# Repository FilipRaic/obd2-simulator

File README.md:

# OBD-II Simulator

Open-source OBD-II simulator board that answers a diagnostic tool over CAN
exactly as a vehicle ECU does. The repository has three parts:

- the **protocol core** (`include/`, `src/`, `tests/`) - portable,
  host-testable protocol and simulation layers with no external
  dependencies, described below,
- the **firmware** (`firmware/`) - PlatformIO project for the device
  itself (FreeRTOS tasks, MCP2515 SPI driver, TFT_eSPI user interface,
  16 MB SPI NOR flash storage with USB-C MSC / USB-A stick transfer), which
  compiles the core unchanged and plugs into it through the small set of
  `extern` platform hooks listed below. See `firmware/README.md`,
- the **board** (`hardware/`) - the KiCad project, gerbers, bill of
  materials and the scripts that generate the board, at revision **v0.7**
  (130 x 115 mm, two-layer FR4, ESP32-S3-WROOM-1). See `hardware/README.md`.

The simulator answers a diagnostic tool over CAN and, like a real vehicle, powers
it from pin 16 of the J1962 connector. The protocol core described below is what
runs inside the "Microcontroller" block, and everything around it is documented
in [`hardware/README.md`](hardware/README.md), which walks through the same
schematics one design decision at a time.

Everything in the repository is in English. The project also keeps a set of
Croatian working documents, which live outside it.

The **v0.7 board has been fabricated and assembled** in one unit. A commercial
ELM327 adapter connects to it, reads all 21 parameters and the fault codes, and
draws its own 12 V from pin 16 while doing so.

## The website

The project has a landing page at **<https://filipraic.github.io/obd2-simulator/>**,
which is the short version of everything below: what the device does, what it is
built from and where to get the files. Two things on it are worth opening even if
the page itself is skipped, because neither can be shown in a README:

| Page | What it is |
|---|---|
| [The user interface demo](https://filipraic.github.io/obd2-simulator/UI-demo/) | the screens `firmware/src/ui/screens/` draws on the display, redrawn in a browser and walked with the same encoder and joystick controls the device has, so the interface can be tried before anything is built |
| [The interactive board view](https://filipraic.github.io/obd2-simulator/OBD2-board-v0.7/) | the v0.7 board drawn in the browser, with the tracks, the ground pour, the vias, the pads and the components as five layers that switch on and off, and a tooltip on every part. Generated from `obd2-simulator.kicad_pcb` by `hardware/kicad/scripts/generate_pcb_html.py` |

## Where to read what

The wiki is written for someone using or rebuilding the device. The files in
this repository are the record of how it was built and why. The wiki is in
English, which is the language of the project. A Croatian translation of the
same pages exists but is not published yet, and if it goes up it will take an
`-HR` suffix, leaving the page names below unchanged.

| Question | Wiki page | In this repository |
|---|---|---|
| What is this and what can it do | [Home](../../wiki/Home) | this file |
| How do I build one | [Building the device](../../wiki/Building-the-device) | [`hardware/README.md`](hardware/README.md), and [`hardware/gerber/README.md`](hardware/gerber/README.md) before ordering |
| How do I compile and flash it | [Firmware](../../wiki/Firmware) | [`firmware/README.md`](firmware/README.md), and [`firmware/tools/README.md`](firmware/tools/README.md) when the ordinary upload path is unavailable |
| How do I drive it | [Usage](../../wiki/Usage) | [`scenarios/README.md`](scenarios/README.md) for the JSON format |
| How do I contribute | [Contributing](../../wiki/Contributing) | the conventions below |
| How is the board generated | - | [`hardware/kicad/scripts/README.md`](hardware/kicad/scripts/README.md) |

Two internal documents govern changes to this project, and neither is published
here: `docs/MAPA-POVEZANIH-DATOTEKA.md` is an "if you change X, check Y" table,
because the same fact is written down in up to six places, and
`docs/combined/DNEVNIK-IZMJENA.md` is the chronological record of every decision.
Both are in Croatian and are working notes rather than product documentation, so
`docs/` is deliberately left out of the repository.

## Modules

| File | Purpose |
|------|---------|
| `include/obd2_pids.h` | Mode/PID constants per SAE J1979 / ISO 15031-5 |
| `include/sensor_table.h` | 21 simulated parameters with ranges and noise |
| `src/pid_encoder.cpp` | Value → raw bytes codec + supported-PID bitmasks |
| `include/dtc_bank.h` | DTC bank (pending/confirmed, MIL, freeze frame) |
| `src/iso_tp.cpp` | ISO 15765-2 transmit path (SF, FF/FC/CF) |
| `src/can_handler.cpp` | Request dispatcher, modes 0x01-0x09 |
| `src/simulator_core.cpp` | Simulation profiles (Manual / Idle / Drive) |
| `tests/test_simulator.cpp` | Host-side unit tests |

Implemented services: 0x01 (current data, 21 PIDs), 0x02 (freeze frame),
0x03/0x07 (stored/pending DTCs), 0x04 (clear DTCs), 0x09 (VIN).
Unsupported services receive the negative response `7F <mode> 11`.
Requests are accepted on 0x7DF (functional) and 0x7E0 (physical), while
responses are sent on 0x7E8. Frames are padded to 8 bytes with 0x55
per ISO 15765-4.

## Platform hooks (implement on target, stubbed in tests)

```cpp
uint32_t millis();                                // ms since boot
void     can_send_frame(const CanFrame& frame);   // MCP2515 transmit
bool     iso_tp_wait_flow_control(FlowControl&);  // wait for FC frame
void     iso_tp_delay_us(uint32_t us);            // STmin pacing
```

## Building and running the tests

```sh
cmake -B build
cmake --build build
ctest --test-dir build --output-on-failure
```

The same tests also run through PlatformIO (`pio test -e native` inside
`firmware/`). Firmware build: `pio run -e custom-board` (the dedicated
ESP32-S3 board, also used on the breadboard adapter during development).

## Regenerating the board

The board is generated rather than drawn: there is no `.kicad_sch`, and the
`.kicad_pcb` is an output. Two entry points, and picking the wrong one costs
work:

```powershell
# a part, a net or the placement changed - rebuilds and re-routes from nothing
powershell -ExecutionPolicy Bypass -File hardware\kicad\scripts\route_board.ps1

# the board file is already right, only the derived files are stale
powershell -ExecutionPolicy Bypass -File hardware\kicad\scripts\regen_outputs.ps1
```

`route_board.ps1` ends by recomputing all 103 reference designator positions and
so **discards the hand-tuned silkscreen**. If no copper moved, run only
`regen_outputs.ps1`. Every step of the chain, what it writes and where, is in
[`hardware/kicad/scripts/README.md`](hardware/kicad/scripts/README.md).

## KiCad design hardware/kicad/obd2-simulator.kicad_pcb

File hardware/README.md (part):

# OBD-II simulator board, revision v0.7

The final hardware of the project: a dedicated two-layer board **130 x 115 mm**
with an ESP32-S3-WROOM-1 module, the CAN chain MCP2515 -> SN65HVD230 ->
PESD1CAN -> J1962F, and power over USB-C Power Delivery.

The five blocks in that diagram are the ones the rest of this document keeps
naming: **power** (USB-C PD to 12 V and 3,3 V), the **CAN and OBD interface**
(MCP2515 to SN65HVD230 to the J1962F socket), the **microcontroller**, **memory
and USB**, and the **user interface**. The dashed arrow is the diagnostic tool,
which the simulator both answers and powers, over pin 16 of the connector.

Every figure in this file is drawn by `kicad/scripts/generate_figures.py`. It
draws them **by hand rather than deriving them from the board**, so a figure does
not follow a board change on its own, and after a change to the schematic it has
to be redrawn there. The full set is listed in [Figures](#figures) below.

The board **has been fabricated and assembled** in one unit, and the core of the
device was verified on it with a commercial ELM327 adapter. Numbers about the
board itself are still measured from the project file
`kicad/obd2-simulator.kicad_pcb` or taken from tool output, never copied from an
earlier version of this text.

Wiki page for anyone building one: **Building the device**, on the repository
wiki. It has the bill of materials, the pinout and the first-power-up procedure. This
file is the design record behind those instructions, decision by decision.

**How the board is generated is a subject of its own**, and it has its own index
in [`kicad/scripts/README.md`](kicad/scripts/README.md): which of the two entry
points to run, what each step of the routing chain is for and which derived file
lands where.

## Board state (measured with the tools)

| Item | State |
|---|---|
| Outline | 130 x 115 mm, two-layer FR4 1,6 mm, 4 x M3 in the corners (spacing 120,00 x 105,00 mm) |
| Footprints | **107** (95 parts to solder + 8 test points + 4 mounting holes), of which **16 SMD** |
| Nets | **64 named**, ground included |
| Routing | **892 segments** (639 top layer, 253 bottom), **73 vias** (72 x 0,60 / 0,30 mm and one x 0,80 / 0,40 mm on V5_STICK), fully routed |
| DRC | **0 errors, 0 warnings, 0 unconnected** (`kicad-cli pcb drc --severity-all`) |
| Mask | black, silkscreen white, ENIG finish |
| Components | all on the top side, the bottom is copper, mask and legend only |

A note on that DRC: it is clean **partly because some rules are switched off**.
The project has `min_silk_clearance = 0` and
`solder_mask_to_copper_clearance = 0`, and `missing_courtyard` is set to
"ignore". The claim "0 warnings" therefore does not by itself mean the silkscreen
has been checked.

**Checked separately on 10.08.2026.** by running DRC over a copy of the project
with those rules restored (`min_silk_clearance` 0,15 mm,
`solder_mask_to_copper_clearance` 0,05 mm, hole spacing 0,50 mm). Outcome:

| Finding | Count | Verdict |
|---|---|---|
| Silkscreen over a pad | **0** | clean, the earlier suspicion is settled |
| Mask bridge between nets | **0** | the openings do not merge, but the bridges are 0,150 mm, see below |
| Silkscreen clipped by the board edge | 2 | J4, 0,140 mm, cosmetic |
| Hole spacing under 0,50 mm | 21 | see `gerber/README.md`, the geometry of connector J1 |
| Footprint type does not match its pads | 1 | U1, an attribute of a custom footprint, no effect on fabrication |

## Contents of this directory

| Contents | What it is |
|---|---|
| `kicad/obd2-simulator.kicad_pcb` | The KiCad board project: footprints, netlist, placement, routing, ground pour, keepout around the antenna |
| `kicad/scripts/` | the scripts that generate the board (KiCad Python API + Freerouting), together with `PRE-FABRICATION-CHECKLIST.md` |
| `kicad/scripts/docx/` | `.docx` tooling that needs no Word: `md2docx.py` builds the technical documentation from Markdown, the rest edit text, tables and the table of contents. Moved here 15.08.2026., has its own `README.md` |
| `kicad/footprints/obd2.pretty/` | custom footprints: CH224K, SEP-A-OBD-D2, SKRHABE010, RK12L12C0A0G |
| `kicad/3dmodels/` | custom VRML models for the render, generated by `scripts/gen_3dmodels.py` |
| `kicad/render-top.png`, `render-bottom.png` | 3D renders of both sides, **embedded in this README**, so a stale render is visible on GitHub |
| `gerber/` | Gerber layers, Excellon drill, gbrjob and the package for the fabricator |
| `schema1.svg` - `schema4.svg`, `blok.svg`, `canchain.svg` | schematics and the block diagram, in English, generated by `scripts/generate_figures.py`. **Not used in the written documentation**, see the note below the table |
| `kicad/scripts/fig/` | every figure the generator draws. The six above are copied up into this directory, and three more are used from here: `zones.svg` (functional zone layout), `nets.svg` (all net groups with their routing rule) and `ip2368.svg` (the external circuit of the CH224K, the file name is that of the part the design started with) |
| `bom/bom-pcb.csv` | parts list with suppliers, order codes and prices |
| `bom/bom-pcb.md` | quantities, values, tolerances and packages, with soldering notes |

The 1:1 print document (`pcb-ispis-1-1-v07.docx`) and the figure generator of
the written documentation (`alati/figgen/`) are **not in this repository**. They
exist only for that document and live beside it. Every other script of
the project, including the ones that write into that directory, has lived here
in `kicad/scripts/` since 15.08.2026.

The **dimensioned drawing** (`tehnicki-crtez-pcb-v07.svg` and `.png`) has lived
there too, in `Slike za rad/crtezi-ploce/`, since 15.08.2026., and
`regen_outputs.ps1` writes it straight into that directory. The English
schematics stay here, because this repository is in English.

The Croatian set of nine figures that used to be generated alongside them **is no
longer produced, and the files that were there have been deleted**. Comparing the
MD5 sums of every image in the written documentation showed nothing uses them, so
`--lang hr` was dropped from `regen_outputs.ps1`. The flag itself still works, if
a Croatian schematic is ever needed:

```powershell
& "$env:LOCALAPPDATA\Programs\KiCad\10.0\bin\python.exe" `
    kicad\scripts\generate_figures.py --lang hr
```

> ⚠️ **The schematics in this directory are not the ones in the written
> documentation.** That document embeds a **different** set of figures, from its
> own generator (`alati/figgen/`). The file names are the same
> (`schema1` to `schema4`, `blok`, `canchain`, `nets`, `zones`), but they are
> different drawings from a different generator. Verified on 15.08.2026. by
> comparing MD5 sums: every PNG from `figgen/out/` is embedded verbatim in that
> `.docx`, and from the board only the render `kicad/render-top.png` and the
> dimensioned drawing `tehnicki-crtez-pcb-v07.png`.
>
> The practical consequence: **changing a schematic here changes nothing in that
> document.** If a figure is needed there too, `figgen` is what gets edited. There
> is no longer a third group of identically named files, because the Croatian
> schematics in `crtezi-ploce/` were deleted on 15.08.2026.

## Figures

Nine drawings, and each one answers a different question. They are used
throughout this document where they explain a decision, and this is the index:

| Figure | Answers |
|---|---|
| [`blok.svg`](blok.svg) | What the device consists of and what talks to what. Start here |
| [`schema1.svg`](schema1.svg) | How 12 V and 3,3 V are made, and where the tool power on pin 16 comes from |
| [`schema2.svg`](schema2.svg) | The CAN interface end to end, MCP2515 to SN65HVD230 to termination to ESD to J1962F |
| [`schema3.svg`](schema3.svg) | The ESP32-S3 module, external flash U7 and the USB subsystem, with the SPI series termination and the test points |
| [`schema4.svg`](schema4.svg) | The user interface: display, encoder, the 5-way switch and the three buttons, with the filters |
| [`canchain.svg`](canchain.svg) | Only the CAN chain, in the order it is actually routed, with the measured distances |
| [`kicad/scripts/fig/zones.svg`](kicad/scripts/fig/zones.svg) | Which functional group sits where on the 130 x 115 mm outline |
| [`kicad/scripts/fig/nets.svg`](kicad/scripts/fig/nets.svg) | Every net group, its ESP32-S3 pins and the rule its routing had to obey |
| [`kicad/scripts/fig/ip2368.svg`](kicad/scripts/fig/ip2368.svg) | The external circuit of the CH224K PD sink, that is how one resistor picks the voltage |

To read the board itself rather than the intent, the two renders below show
what was actually built. They come out of `regen_outputs.ps1`, straight from
`obd2-simulator.kicad_pcb` with the board stackup colours, so they are the
board and not a drawing of it.

The top side carries every component and the whole silkscreen, so this is the
view to compare a placement change against.

The bottom side is copper and pads only, which is why a silkscreen edit leaves
it byte for byte identical while a re-route changes it.

---

# Why the board is the way it is

## Size: 130 x 115 mm

With all-through-hole passives every pad blocks **both** layers, so a two-layer
autorouter quickly runs out of corridors. Tried and documented:

| Size | Resistors | Result |
|---|---|---|
| 100 x 80 | vertical | at least one net always fails (CC2, then BTN_CLEAR, then JOY_SW) |
| 100 x 90 | vertical | JOY_SW and CS_FLASH fail |
| 105 x 100 | vertical | everything routes |
| 115 x 100 | horizontal | everything routes, but with no room for the 17 extra footprints the review asks for |
| **130 x 115** | **horizontal** | **107 footprints, every net routed, DRC clean** |

The space was added by moving the groups **tied to an edge** out to the new edge
and leaving the rest where it was. That opened two free bands into which the
packer drops the new parts: a vertical one at x = 96..111 and a horizontal one at
y = 84..99.

The zone map shows what "the groups tied to an edge" means. The OBD connector J2
and USB-C J1 share the top edge, USB-A J4 sits on the bottom one, and the whole
user interface stands on a single vertical axis along the right edge, so the
parts that must reach a connector never have to cross the board. What is left in
the middle is the routing space the numbers above are about.

Signal tracks were narrowed from 0,25 to **0,20 mm**. The gap between two THT
pads on a 2,54 mm grid is about 0,94 mm, so those 0,05 mm decide whether a net
gets through. The documentation allows 0,15 mm, currents are below 0,5 A per
branch, and ground is a pour.

Four short supply nets (SW_3V3, SW_5V, V5_STICK, VBUS_STICK) have their own
**Power class with a 0,40 mm width**. This is not a repeat of the abandoned
attempt with net OBD_12V: there, 0,50 mm went to a long track crossing the whole
board and closed the corridor used by CS_FLASH and BTN_RETURN, so the board
failed DRC. These four are short and local, right at the converters and at the
USB-A socket, and cross no corridor.

## The power section respects the TPS562201 datasheet

The schematic is the map for the table below: USB-C into the CH224K, 12 V out of
it to pin 16 of the OBD connector through F1, D3 and D2, and the same 12 V into
the two TPS562201 converters that make 3,3 V and 5 V.

This is the only review finding that changed function rather than tidiness.

| | before | now | Datasheet (SLVSD91D) |
|---|---|---|---|
| L2, L3 | 10 µH | **4,7 µH** | table 7-2: 3,3 µH typ. and 4,7 µH **max** for 3,3 V, 4,7 µH typ. and max for 5 V |
| C3, C4, C27, C28 | plain electrolytic, ESR ~1 Ω | **low ESR, ESR ≤ 0,15 Ω** | 7.2.2.3: "ceramic or other low-ESR capacitors, 20 to 68 µF" |
| Ripple on 3,3 V | about 0,9 V | **about 30 mV** | |
| C at the input of U10 | only 100 nF (nearest electrolytic 73 mm away) | **C37, 10 µF right at the pin** | |

Those two items were linked. The inductor had once been raised from 2,2 to 10 µH
to cut the ripple current through the electrolytic, which treated the symptom.
The cause was the choice of capacitor. Now that they are low ESR, the inductor
can go back into the range the manufacturer specifies.

**The criterion is impedance, not chemistry** *(rewritten 10.08.2026.)*. It used
to demand a polymer part explicitly, even though the datasheet says "ceramic
**or other low-ESR**". The measurable form is **ESR at 100 kHz ≤ 0,15 Ω** with a
**rated ripple current ≥ 0,35 A rms**. Those capacitors carry 0,88 A peak to peak
on the 3,3 V rail and 1,07 A on the 5 V rail:

| Capacitor | ESR | Ripple on 3,3 V | Ripple on 5 V | Verdict |
|---|---|---|---|---|
| Polymer | 20 to 50 mΩ | 26 mV | 32 mV | ideal |
| Electrolytic marked "low ESR" | up to 150 mΩ | 132 mV | 161 mV | **usable, this is what is fitted** |
| Plain electrolytic | about 1 Ω | 878 mV | 1070 mV | unusable |

The ESP32-S3 wants 3,0 to 3,6 V and the flash 2,7 to 3,6 V. At 132 mV the rail
moves between 3,234 and 3,366 V, with margin. With a plain electrolytic it moves
between 2,86 and 3,74 V, outside the specification of both chips, and the ripple
current of 0,25 to 0,31 A is above what a part of that size can take anyway.

If the measured ESR turns out worse than 0,15 Ω, the answer is not a different
electrolytic but a **ceramic 4,7 to 10 µF across the same pads**: at 580 kHz its
impedance is some tens of mΩ and it takes over the ripple current.

The lower member of the 3,3 V feedback divider is not a single 15,4 kΩ resistor
but **two in series, R17A = 15 kΩ and R17B = 470 Ω**, joined by net `FB_MID`. The
reason is availability: 15,4 kΩ exists only in the E96 series and could not be
bought in a through-hole part.

| Lower member | Output |
|---|---|
| 15 kΩ + 470 Ω = 15,47 kΩ (as built) | **3,300 V** |
| 15,4 kΩ (originally) | 3,311 V |
| 15 kΩ alone | 3,379 V, **unusable** |

With the feedback tolerance, 15 kΩ on its own heads towards 3,45 V, and the NOR
flash U7 has an absolute maximum of 3,6 V, so no margin would be left. The series
pair does not worsen the tolerance (±150 Ω plus ±4,7 Ω on 15,47 kΩ is still
±1 %), and dissipation is irrelevant, 49,6 µA flows through the divider.

## The CH224K does not sit on the data pair

The whole PD side of the board is that one figure: the CC lines to the
controller, a single resistor to pick the voltage, and the charger puts it on
VBUS. Note that DP and DM leave the controller unconnected, and this is why.

The DP and DM pins of the controller used to be connected to USBC_DP and
USBC_DM, that is to the same pair the ESP32 uses to talk to a PC, which is also
the primary programming path (USB-Serial-JTAG) and the MSC mode. Section 5.5 of
the CH224 datasheet says, verbatim: *"If you want to shield these protocols on
CH224K/CH224D, you need to disconnect the DP/DM pin of CH224K/CH224D from the
Type-C interface."* The PD contract is negotiated purely over the CC lines, so
those two pins are left unconnected.

## The CAN pair is a chain, not a tree

The first figure is the prescribed order together with the distances actually
achieved, the second is the same chain with the parts around it: the 8 MHz
crystal Y1 on the MCP2515, the SPI lines back to the module, and the 12 V that
leaves for pin 16 of the connector. The order is the point: the 120 Ω
termination R7 comes before the ESD diode D1, and D1 sits as close to the
connector as the 43,3 x 20,7 mm connector body allows, 9,0 mm from pin 14.

The checklist asks for `SN65HVD230 -> R7 -> D1 -> J1962F` without branches,
without vias and with roughly equal lengths. Machine-routed, the pair was none of
that:

| | machine-routed | now |
|---|---|---|
| Topology | R7 is a node with **three branches**, D1 hangs off a 13,0 mm stub (CANH) and a 4,3 mm one (CANL) | a chain, no branching |
| Vias | 1 on CANL, 0 on CANH | **0 on both** |
| Layers | both pairs across F.Cu and B.Cu | both on **F.Cu only** |
| Lengths | 73,7 and 56,9 mm, difference 16,8 mm | 83,9 and 62,2 mm, difference 21,7 mm |

The cause was not the placement but the fact that Freerouting routes a minimal
tree and knows nothing about a prescribed order. The placement was improved (D1
anchors to the connector, R7 to D1, the test points to D1), but placement alone
cannot force a topology on the router. The pair is therefore routed by its own
script, `kicad/scripts/route_can_chain.py`, and it runs **before** Freerouting,
while the top layer is still empty. `dsn_export.py` hands those tracks over as
immovable (`(type protect)` instead of `(type route)`), so the router routes
around them.

The length difference stayed at about 20 mm and cannot get smaller without moving
parts: it comes from the leads of termination R7 being 10,16 mm apart and the two
pin rows of connector J1962F being 8,6 mm apart, 18,8 mm together. At 500 kbit/s
that is 0,13 ns on a bit of 2000 ns.

## Smaller, but real findings

| Finding | Fix |
|---|---|
| On 09.08. D3 was switched to a Schottky SS34 on the claim that a TVS has no rating for continuous forward current | **withdrawn 10.08.2026., D3 is an SMAJ16A again.** The datasheet gives `PD` = 3,3 W and `RθJA` = 120 °C/W, and the worst case is 0,45 W. See the section below |
| Both USB connectors without any ESD protection, while the CAN pair has D1 | **D4, D5** (USBLC6-2SC6). Pin 5 to +3,3 V, not to VBUS, because its standoff is 5,25 V |
| CS_CAN and CS_FLASH float until the firmware takes the pin over | **R35, R36** (10 kΩ pull-up) |
| USB_HOST_EN floats, and the EN of the switch is active high | **R37** (10 kΩ pull-down) |
| A 10 nF encoder filter gives 100 µs, while contact bounce lasts on the order of ms | **47 nF** (470 µs) |
| The filter capacitor discharges straight through the encoder contact, a spike of several amperes through a contact rated for 10 mA | **R38-R40**, 100 Ω in series right at the contact, mounted vertically |
| V5_STICK 100 mm at 0,20 mm, about 0,25 Ω, a quarter of a volt dropped at 1 A | net class **Power, 0,40 mm** on V5_STICK, VBUS_STICK, SW_3V3, SW_5V |
| The inductor footprint drew a Ø5 mm body while the BOM asked for "up to Ø9 mm", so the courtyard was smaller than the part and DRC would not report a collision | footprint at **Ø7,5 mm**, BOM at "up to Ø7,5 mm" |
| The inductor footprint was axial and mounted vertically, so it drew the body over one hole, while the radial part that was bought sits centred between two | **`L_Radial_D8.7mm_P5.00mm_Fastron_07HCP`**, 5,00 mm pitch, BOM at "up to Ø8,5 mm" |
| The board legend was a wish only, the packer knew nothing about it | the space is reserved **before** packing |
| An SPI bus 88 to 126 mm long with three loads and no termination | **R30, R31**, 33 Ω in series right at the module pin, with the new nets SCK_MCU and MOSI_MCU |
| The checklist asks for eight test points and the board had none | **TP1 - TP8**, each beside the pad of its own net, that is in line rather than on a stub |
| The shield of USB-A socket J4 was on no net at all: the script assigned ground to pads "5" and "6" while the footprint calls them `SH` | both tabs on **ground**, joined by the pour flooding on the bottom layer. Found 10.08.2026. by comparing the netlist from the script with the netlist of the finished board |

## ENC1: an incremental encoder instead of a potentiometer

Everything the user touches is in this one figure: the ILI9341 display, encoder
ENC1 with its filter at both ends, the 5-way switch SW6 on the resistor ladder,
and the three CONFIRM / CLEAR / RETURN buttons.

The rotary potentiometer was replaced by an **incremental encoder with a
button**, a BI Technologies EN11-HSB1AQ20, 20 pulses and 20 detents per
revolution.

| | potentiometer | encoder |
|---|---|---|
| Kind of signal | analogue, absolute position | digital, relative steps |
| Pins | GPIO1 (ADC1_CH0) | GPIO1 (A), GPIO38 (B), GPIO39 (button) |
| Nets | POT | ENC_A, ENC_B, ENC_SW |
| Firmware | ADC read, filter, hysteresis, correction of the logarithmic law | quadrature decoder in an interrupt handler, step size depending on turn speed |

That removed the function `pot_linearize()` from the firmware, which existed only
because the potentiometer that had been bought had a logarithmic (audio) 15A law.

**The footprint is the stock KiCad
`RotaryEncoder_Alps_EC11E-Switch_Vertical_H20mm`**, not a custom one. The EN11
belongs to the same family of 11 mm encoders and has the same lead arrangement:
A, C and B on a 2,5 mm pitch on one side, two button contacts on the other and
two mounting tabs. Using a ready-made, proven footprint is considerably safer
than drawing a new one, but **it is also the one item that must be measured
before the board is ordered**.

Resolution is handled by acceleration: the step is 1/256 of the range on a slow
turn, 1/64 on a medium one and 1/16 on a fast one, so the full range is crossed
in roughly one quick turn.

The shaft falls on the interface axis x = 104 at height y = 69, exactly where the
potentiometer shaft used to be. Joystick SW6 and the CONFIRM, CLEAR and RETURN
buttons share that vertical axis.

## D3 is an SMAJ16A, not a Schottky

The blocking diode on the branch towards pin 16 exists because F1 is a PTC fuse
and conducts both ways, so external 12 V from a vehicle or from a tool that
powers the line itself would flow back into `VBUS`, into the inputs of both
converters and onto the USB-C connector.

Between 09.08. and 10.08.2026. an **SS34** stood there, on the grounds that a TVS
diode has no rating in its datasheet for continuous forward current, only `IFSM`
for an 8,3 ms pulse. **That reasoning was too strict and has been withdrawn.**

The SMAJ series datasheet (Littelfuse, rev. 10/2020) gives exactly what is needed
to bound continuous forward operation: `PD` = **3,3 W** and `RθJA` =
**120 °C/W**. Only the `IF(AV)` figure is missing, not the thermal data. F1 limits
the branch to 500 mA, and a scan tool draws 25 to 50 mA:

| | 50 mA (ELM327) | 500 mA (F1 limit) |
|---|---|---|
| Power in the diode | 35 mW | **0,45 W** out of 3,3 W |
| Junction temperature rise | 4 °C | **54 °C**, junction at about 79 °C out of 150 °C |
| Voltage at pin 16 | about 11,3 V | about 11,1 V |
| The same with an SS34 | 11,7 V | 11,6 V |

So there never was a thermal problem, and the voltage difference is about 0,4 V,
while tools per J1979 work from roughly 9 V upwards.

| | SS34 | SMAJ16A |
|---|---|---|
| Reverse voltage | 40 V | **16 V**, breakdown 17,8 to 19,7 V |
| Reverse leakage | hundreds of µA, milliamperes at 100 °C | **< 1 µA** |
| Forward drop at 50 mA | about 0,45 V | about 0,7 V |
| Sourcing | a new type | **already ordered, a second piece alongside D2** |

The concession is reverse margin above 18 V, and that only matters if the
simulator is ever plugged into a real vehicle. This board is the source of those
12 V, not a consumer. In exchange the leakage is a thousand times lower, and
blocking is the only purpose of that diode.

The swap does not touch the board: the same SMA package (DO-214AC), the same
`D_SMA` footprint, and **pad 1 is the cathode on both**, so the same orientation
and the same silkscreen. D2 and D3 thereby become the same part and cannot be
mixed up when soldering.

## Corrected polarity of TVS diode D2

In the first prototype D2 was connected with its **cathode to ground and its
anode to +12 V** (pad 1 = GND, pad 2 = OBD_12V). Pad 1 is the cathode by KiCad
convention, and the SMAJ16A is a unidirectional TVS (a bidirectional one would be
an SMAJ16**CA**). Connected that way the TVS conducts forward at about 0,8 V and
effectively shorts the 12 V branch towards pin 16 of the connector, tripping the
PTC fuse continuously. Now **pad 1 (cathode) is on OBD_12V and pad 2 (anode) on
ground**.

## Every passive is through-hole

Resistors, capacitors and inductors are through-hole parts. What stays SMD is the
**integrated circuits, the module, the diodes, the fuse and the joystick**, 16
footprints in total: U1 CH224K, U2 and U11 TPS562201, U4 MCP2515,
U5 SN65HVD230, U6 module, U7 flash, U9 TS3USB221, U10 SY6280, D1 PESD1CAN, D2 and
D3 SMAJ16A, D4 and D5 USBLC6-2SC6, F1 1206L050 and SW6 SKRHABE010.

D4 and D5 carry the DNP flag, so a board assembled without them has 14 SMD parts.
The figure comes from counting footprints with `(attr smd)` in the `.kicad_pcb`,
and that is how it should be checked, because a list written out by hand is
easily left short.

The fuse and the TVS deliberately stayed SMD: they are neither resistor, nor
capacitor, nor inductor, and those packages solder easily with a hand iron, so
there is no reason to spend space on through-hole substitutes. Joystick SW6 has
no through-hole version.

The resistors **lie flat**, on a **10,16 mm** pitch with a DIN0207 body
(6,3 x 2,5 mm), that is a standard 1/4 W resistor. That pitch also takes smaller
bodies, since leads can always be spread wider. Vertical mounting (2,54 mm pitch)
would save about 590 mm² across 21 resistors, but is harder to hand-solder.

**The only exception is R38-R40**, the series resistors in the encoder filter,
which stand vertically on a 5,08 mm pitch. That is out of necessity rather than
thrift: they have to sit right at the encoder contact, and the column along the
right-hand edge already carries the encoder, the joystick, three buttons and nine
pull-ups.

The ceramic capacitors are on a **5 mm** pitch, because that is how they are
sold. Without it the part that was bought could not be pushed into the board.

## Placement: the order is electrical, not tabular

Parts that must sit next to a particular pad are placed by **priority**, not in
the order of the component table. The rule: the faster the loop, the earlier it
goes. Nine parts compete around a single SOT-23 converter, and a ring of 12 mm
radius has about 490 mm², just enough for all of them, but only if the most
important ones choose first. In table order the first to choose was C1, a 100 µF
bulk capacitor to which proximity means nothing, while bootstrap C21 ended up at
12,5 mm.

On top of that **all four rotations** are tried and the distance is measured **to
the pad on the same net**, not to the footprint origin. A horizontal resistor is
10,16 mm long between its holes, so by the old measurement R16 was "11,5 mm from
the FB pin" while it really was 21,1 mm, because it faced the wrong way.

### Measured distances to supply and sensitive pins

| Connection | before | now |
|---|---|---|
| C21 bootstrap to the BST pin of U2 | 14,0 mm | **5,8 mm** |
| C29 bootstrap to the BST pin of U11 | 15,5 mm | **4,2 mm** |
| L2 to the SW pin of U2 | 9,2 mm | **6,5 mm** |
| L3 to the SW pin of U11 | 20,9 mm | **7,5 mm** |
| C15 to pin 2 of the module | 14,0 mm | **3,5 mm** |
| C16 to pin 2 of the module | 18,5 mm | **5,5 mm** |
| Y1 to OSC1 | 7,3 mm | **6,0 mm** |
| R7 termination to J2.14 | 18,5 mm (to pin 6) | **9,5 mm** |
| D1 ESD to J2.14 | 18,6 mm (to pin 6) | **9,4 mm** |
| R30 to pin 20 of the module | - | 4,0 mm |
| D3 to F1 | - | 4,6 mm |

| Net | before | now |
|---|---|---|
| FB_3V3 | 39,4 mm | **24,6 mm** |
| FB_5V | 57,9 mm | **32,1 mm** |
| SW_3V3 | 30,1 mm | **25,0 mm** |
| SW_5V | 42,3 mm | **20,4 mm** |
| MOSI | 100,3 mm | 91,6 mm |
| MISO | 91,6 mm | 87,7 mm |
| SCK | 105,3 mm | 125,9 mm |
| CANH / CANL | 61,9 / 60,9 mm | 73,8 / 57,9 mm |
| VBUS | 114,6 mm | 201,2 mm |

Several nets are longer than before. The board is 15 mm wider and 15 mm taller,
so anything crossing it grows by about 15 %. VBUS is longer because bulk
capacitor C1 moved from the converter input to the VBUS pin of the USB-C
connector, where it belongs, giving the net one more long arm.

The net overview is what a change gets checked against before it touches the
board: which ESP32-S3 pin carries which signal, and what rule that group is
routed under. The rules easiest to break by accident are the 33 Ω series
resistors at the source of the SPI bus, the CAN pair with no stubs and no vias
entirely on the top layer, and the 0,40 mm Power class on the four short supply
nets.

## Silkscreen

Reference designators (R1, C3, U6 …) are on the top silkscreen, **all horizontal,
all 0,9 mm high and all beside their part**. Silkscreen over a track is
**allowed**: it is printed over the solder mask, that is after the copper, so an
overlap with a track has no consequence. What is not conceded is a designator
over a pad, over another designator, or outside the board outline.

**The final designator placement was hand-tuned in KiCad** and is authoritative
as it stands in the `.kicad_pcb`. The script
`kicad/scripts/place_silk_after_route.py` only provides a starting placement, and
**running it will overwrite the manual work**. The list of those manual changes
is in the header of the script itself. The tuning went in two rounds, on
10.08.2026. and 11.08.2026., the second of which moved 59 designators. After such
an edit, run **only** `regen_outputs.ps1`, because `route_board.ps1` calls that
script at the end and puts the designators back where it computed them.

The board legend is two lines, `OBD-II SIMULATOR v0.7` and
`Designed by Filip Raic`, on both sides. Its space is reserved in the packer
before parts start to be placed, otherwise the first part landing in that band
pushes the legend into a corner.

## A fixed generator bug: the module outline

On the first routed version resistor R25 stood **under the module PCB of U6**, in
the corner by the antenna. The cause was not the placement but the generator:
`build_board.py` redrew the module's courtyard around the **bounding box of the
pads**, and the antenna end of the module has no pads at all. The courtyard came
out 6,5 mm shorter than the module itself:

| | x range |
|---|---|
| Courtyard the script drew | 24,50 .. **44,26** |
| The actual module body (F.Fab) | 25,25 .. **50,75** |

To the packer that piece of the module looked like empty space. **DRC did not
report it**, because DRC compares courtyards and the courtyard was too short. The
real outline from the F.Fab layer is used now, and R25 sits **19,9 mm from the
module body**.

A second bug was fixed along the way: the first version of the fix computed the
bounding box through `BOX2I.Merge`, which gave **a different result on two
consecutive runs**, because `GetBoundingBox()` through SWIG returns a temporary
that does not survive the next call. Every bounding box is now converted to plain
numbers immediately.

## Frozen placement: why there is none at the moment

`kicad/scripts/placement_locked.py` can hold the coordinates of every part and
thereby make regeneration repeatable. It is **empty** at the moment, so the
packer computes the placement.

The reason is that the freeze was made while the board was 115 x 100 mm and the
packer was overloaded, and it cemented exactly what the review calls out as bad:
bootstrap capacitors 14 to 16 mm from their pins, C7 seventeen millimetres from
OSC2, the ESD diode nineteen millimetres behind the OBD connector. The intent
behind `NEAR_OF` in `build_board.py` was the opposite, but `LOCKED` overrode
`NEAR_OF`.

At 130 x 115 mm the packer has room, so `NEAR_OF` decides again. If a placement
is ever settled and worth freezing, the coordinates are dumped from the finished
board and put back into that file.

On how sensitive the packer is, a warning from practice: introducing **one single
resistor** (R17B) produced three different collapses in three attempts, the worst
of which broke nine nets, because it pushed one capacitor into the corridor
carrying SPI and all three button lines.

---

# How the board is generated

The whole chain (placement, CAN pair, routing, ground repair, DRC):

```powershell
powershell -ExecutionPolicy Bypass -File kicad\scripts\route_board.ps1
```

Derived files only (renders, gerbers, drawing, schematics, HTML), without
re-routing:

```powershell
powershell -ExecutionPolicy Bypass -File kicad\scripts\regen_outputs.ps1
```

**Neither script is optional after a board change.** Both renders are embedded
in this README, so anything that changes the board and is not followed by
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
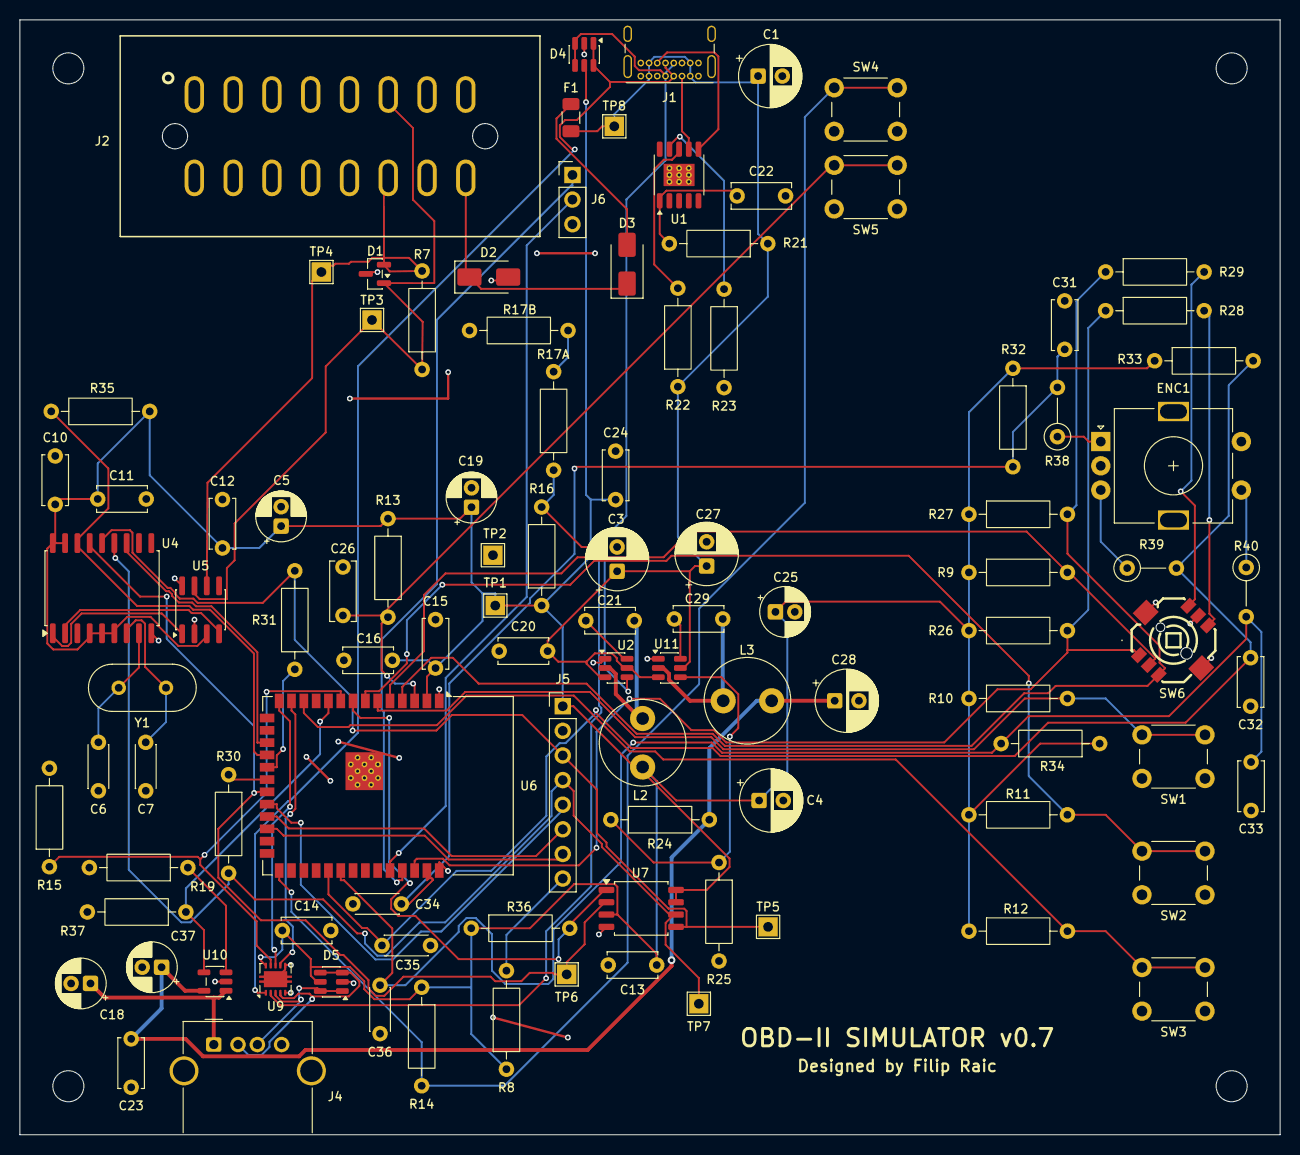
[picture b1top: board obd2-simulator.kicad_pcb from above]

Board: 2 copper layers, 130.0 x 115.0 mm, 107 parts (0 on the bottom side), 64 nets.

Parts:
C1: 100uF/25V; CP_Radial_D6.3mm_P2.50mm
C3, C4, C27, C28: 22uF LowESR; CP_Radial_D6.3mm_P2.50mm
C5, C18, C19, C25, C37: 10uF; CP_Radial_D5.0mm_P2.00mm
C6, C7: 22pF; C_Disc_D4.3mm_W1.9mm_P5.00mm
C10, C11, C12, C13, C14, C15, C16, C20, C21, C23, C24, C29: 100nF; C_Disc_D5.0mm_W2.5mm_P5.00mm
C22, C26: 1uF; C_Disc_D6.0mm_W2.5mm_P5.00mm
C31, C32, C33: 47nF; C_Disc_D5.0mm_W2.5mm_P5.00mm
C34, C35, C36: 1nF; C_Disc_D4.3mm_W1.9mm_P5.00mm
D1: PESD1CAN; SOT-23
D2, D3: SMAJ16A; D_SMA
D4, D5: USBLC6-2SC6; SOT-23-6
ENC1: EN11-HSB1AQ20; RotaryEncoder_Alps_EC11E-Switch_Vertical_H20mm
F1: PTC 500mA; Fuse_1206_3216Metric
H1, H2, H3, H4: M3; MountingHole_3.2mm_M3
J1: USB-C; USB_C_Receptacle_GCT_USB4085
J2: J1962F OBD-II; SEP-A-OBD-D2
J4: USB-A; USB_A_Molex_67643_Horizontal
J5: LCD 18366; PinHeader_1x08_P2.54mm_Vertical
J6: UART; PinHeader_1x03_P2.54mm_Vertical
L2, L3: 4u7H; L_Radial_D8.7mm_P5.00mm_Fastron_07HCP
R7: 120R; R_Axial_DIN0207_L6.3mm_D2.5mm_P10.16mm_Horizontal
R8, R30, R31: 33R; R_Axial_DIN0207_L6.3mm_D2.5mm_P10.16mm_Horizontal
R9, R10, R11, R12, R13, R14, R15, R22, R28, R29, R32, R33, R34, R35, R36, R37: 10k; R_Axial_DIN0207_L6.3mm_D2.5mm_P10.16mm_Horizontal
R16, R24: 51k; R_Axial_DIN0207_L6.3mm_D2.5mm_P10.16mm_Horizontal
R17A: 15k; R_Axial_DIN0207_L6.3mm_D2.5mm_P10.16mm_Horizontal
R17B: 470R; R_Axial_DIN0207_L6.3mm_D2.5mm_P10.16mm_Horizontal
R19, R26, R27: 6k8; R_Axial_DIN0207_L6.3mm_D2.5mm_P10.16mm_Horizontal
R21: 1k; R_Axial_DIN0207_L6.3mm_D2.5mm_P10.16mm_Horizontal
R23: 24k; R_Axial_DIN0207_L6.3mm_D2.5mm_P10.16mm_Horizontal
R25: 9k31; R_Axial_DIN0207_L6.3mm_D2.5mm_P10.16mm_Horizontal
R38, R39, R40: 100R; R_Axial_DIN0207_L6.3mm_D2.5mm_P5.08mm_Vertical
SW1: CONFIRM; SW_PUSH_6mm
SW2: CLEAR; SW_PUSH_6mm
SW3: RETURN; SW_PUSH_6mm
SW4: BOOT; SW_PUSH_6mm
SW5: RESET; SW_PUSH_6mm
SW6: SKRHABE010
TP1: 3V3; TestPoint_THTPad_2.0x2.0mm_Drill1.0mm
TP2: GND; TestPoint_THTPad_2.0x2.0mm_Drill1.0mm
TP3: CANH; TestPoint_THTPad_2.0x2.0mm_Drill1.0mm
TP4: CANL; TestPoint_THTPad_2.0x2.0mm_Drill1.0mm
TP5: MOSI; TestPoint_THTPad_2.0x2.0mm_Drill1.0mm
TP6: MISO; TestPoint_THTPad_2.0x2.0mm_Drill1.0mm
TP7: SCK; TestPoint_THTPad_2.0x2.0mm_Drill1.0mm
TP8: VBUS; TestPoint_THTPad_2.0x2.0mm_Drill1.0mm
U1: CH224K; CH224K_ESSOP-10-1EP_3.9x5.0mm_P1mm_EP2.3x3.2mm
U2, U11: TPS562201DDCR; SOT-23-6
U4: MCP2515-I/SO; SOIC-18W_7.5x11.6mm_P1.27mm
U5: SN65HVD230DR; SOIC-8_3.9x4.9mm_P1.27mm
U6: ESP32-S3-WROOM-1
U7: S25FL128LAGMFM010; SOIC-8_5.3x5.3mm_P1.27mm
U9: TS3USB221; Texas_DRC0010J
U10: SY6280AAC; SOT-23-5
Y1: 8MHz; Crystal_HC49-U_Vertical

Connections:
+3V3: C4.1, C5.1, C10.1, C11.1, C12.1, C13.1, C14.1, C15.1, C16.1, C19.1, C24.1, C25.1, D4.5, D5.5, J5.1, L2.2, R8.1, R9.1, R10.1, R11.1, R12.1, R13.1, R14.1, R16.1, R26.1, R27.1, R32.1, R33.1, R34.1, R35.1, R36.1, TP1.1, U4.4, U4.5, U4.6, U4.17, U4.18, U5.3, U6.2, U7.3, U7.7, U7.8, U9.10
BOOT: R14.2, SW4.1, U6.27
BST_3V3: C21.2, U2.6
BST_5V: C29.2, U11.6
BTN_CLEAR: R11.2, SW2.1, U6.7
BTN_CONFIRM: R10.2, SW1.1, U6.6
BTN_RETURN: R12.2, SW3.1, U6.12
CANH: D1.1, J2.6, R7.1, TP3.1, U5.7
CANL: D1.2, J2.14, R7.2, TP4.1, U5.6
CAN_RX: U4.2, U5.4
CAN_TX: U4.1, U5.1
CC1: J1.A5, U1.7
CC2: J1.B5, U1.6
CS_CAN: R35.2, U4.16, U6.18
CS_FLASH: R36.2, U6.8, U7.1
CS_TFT: J5.5, U6.22
ENC_A: C31.1, C34.1, R32.2, R38.2, U6.39
ENC_A_RAW: ENC1.A, R38.1
ENC_B: C32.1, C35.1, R33.2, R39.2, U6.31
ENC_B_RAW: ENC1.B, R39.1
ENC_SW: C33.1, C36.1, R34.2, R40.2, U6.32
ENC_SW_RAW: ENC1.S1, R40.1
FB_3V3: R16.2, R17A.1, U2.4
FB_5V: R24.2, R25.1, U11.4
FB_MID: R17A.2, R17B.1
FUSED_12V: D3.2, F1.2
GND: C1.2, C3.2, C4.2, C5.2, C6.2, C7.2, C10.2, C11.2, C12.2, C13.2, C14.2, C15.2, C16.2, C18.2, C19.2, C20.2, C22.2, C23.2, C24.2, C25.2, C26.2, C27.2, C28.2, C31.2, C32.2, C33.2, C34.2, C35.2, C36.2, C37.2, D1.3, D2.2, D4.2, D5.2, ENC1.C, ENC1.MP, ENC1.S2, J1.A1, J1.A12, J1.B1, J1.B12, J1.SH, J2.4, J2.5, J4.4, J4.SH, J5.2, J6.3, R15.2, R17B.2, R19.2, R23.2, R25.2, R37.2, SW1.2, SW2.2, SW3.2, SW4.2, SW5.2, SW6.5, SW6.7, SW6.8, TP2.1, U1.0, U2.1, U4.9, U5.2, U5.8, U6.1, U6.40, U6.41, U7.4, U9.5, U9.6, U9.11, U10.2, U11.1
INT_CAN: U4.12, U6.17
ISET: R19.1, U10.3
JOY_SW: R9.2, SW6.2, U6.5
JOY_X: R26.2, R28.1, SW6.1, U6.38
JOY_XB: R28.2, SW6.6
JOY_Y: R27.2, R29.1, SW6.3, U6.4
JOY_YB: R29.2, SW6.4
MCU_EN: C26.1, R13.2, SW5.1, U6.3
MISO: TP6.1, U4.15, U6.21, U7.2
MOSI: J5.3, R31.2, TP5.1, U4.14, U7.5
MOSI_MCU: R31.1, U6.19
OBD_12V: D2.1, D3.1, J2.16
PD_CFG1: R23.1, U1.9
PD_SENSE: R22.2, U1.8
PD_VDD: C22.1, R21.2, U1.1
RXD0: J6.2, U6.36
SCK: J5.4, R30.2, TP7.1, U4.13, U7.6
SCK_MCU: R30.1, U6.20
SW_3V3: C21.1, L2.1, U2.2
SW_5V: C29.1, L3.1, U11.2
TFT_DC: J5.6, U6.23
TFT_LED: J5.8, R8.2
TFT_RST: J5.7, U6.24
TXD0: J6.1, U6.37
USBA_DM: D5.3, D5.4, J4.2, U9.4
USBA_DP: D5.1, D5.6, J4.3, U9.3
USBC_DM: D4.3, D4.4, J1.A7, J1.B7, U9.2
USBC_DP: D4.1, D4.6, J1.A6, J1.B6, U9.1
USB_DM: U6.13, U9.7
USB_DP: U6.14, U9.8
USB_HOST_EN: R37.1, U6.10, U10.4
USB_SEL: R15.1, U6.9, U9.9
V5_STICK: C23.1, C28.1, C37.1, L3.2, R24.1, U10.5
VBUS: C1.1, C3.1, C20.1, C27.1, F1.1, J1.A4, J1.A9, J1.B4, J1.B9, R21.1, R22.1, TP8.1, U2.3, U2.5, U11.3, U11.5
VBUS_STICK: C18.1, J4.1, U10.1
XTAL1: C6.1, U4.8, Y1.1
XTAL2: C7.1, U4.7, Y1.2

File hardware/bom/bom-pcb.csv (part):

Block,Component,Description / references,Qty,Package / pitch,Sourcing,Note
Processor,ESP32-S3-WROOM-1-N8R2,"dual-core 240 MHz, 8 MB flash, 2 MB PSRAM (U6)",1,SMD module,LCSC (C2913204),unchanged
CAN,MCP2515-I/SO,"CAN 2.0B controller, SPI (U4)",1,SOIC-18W,LCSC (C12368),"unchanged; Conrad stocks only the I/ST variant in TSSOP-20, a different footprint"
CAN,SN65HVD230DR,"CAN transceiver 3,3 V, ISO 11898 (U5)",1,SOIC-8,LCSC (C12084),unchanged
CAN,Crystal 8 MHz,"ABL-8.000MHZ-B2, +-20 ppm (Y1)",1,HC-49/U vertical,LCSC (C7060573),unchanged
OBD,J1962 female,"MINITOOLS SEP-A-OBD-D2, 16-pin, now directly on the board (J2)",1,THT custom footprint,TME (A-OBD-D),unchanged
OBD,PESD1CAN,ESD protection for the CAN bus (D1),1,SOT-23,TME (PESD1CAN.215),unchanged
UI,"Waveshare 18366, TFT 2,4""","ILI9341, 320 x 240, SPI, no touch; connects to J5",1,module,TME (WSH-18366),unchanged
UI,Tactile button 6 mm,"SW1 CONFIRM, SW2 CLEAR, SW3 RETURN, SW4 BOOT, SW5 RESET",5,THT 6x6 mm,TME (1825967-1),"unchanged; the footprint has 4 holes 6,5 x 4,5 mm and matches the buttons in stock"
UI,SKRHABE010,"Alps 5-way switch, directly on the board (SW6)",1,SMD custom footprint,TME (SKRHABE010),unchanged
UI,Incremental encoder,"BI Technologies EN11-HSB1AQ20, 20 pulses and 20 detents per revolution, with a built-in button, directly on the board (ENC1)",1,"THT, stock footprint RotaryEncoder_Alps_EC11E-Switch_Vertical_H20mm",TME (EN11-HSB1AQ20),CHANGED 06.08.2026.: replaced potentiometer RV1. Measure the lead pitch with calipers before ordering
Power,USB-C connector,"GCT USB4085-GF-A, USB 2.0 + PD (J1)",1,SMD,TME (USB4085-GF-A),unchanged
Power,CH224K,"USB-C PD sink, negotiates 12 V (U1)",1,ESSOP-10,LCSC (C970725),unchanged
Power,TPS562201DDCR,"buck converter; U2 gives 3,3 V, U11 gives 5 V",2,SOT-23-6,TME (TPS562201DDCR),unchanged
Memory,S25FL128LAGMFM010,"16 MB NOR flash, SPI (U7) - the part actually ordered; an equivalent replacement is the Winbond W25Q128JVSIQ, same package and same pinout",1,SOIC-8 208 mil (SOC008),TME (S25FL128LAGMFM010),footprint value aligned with the ordered part 05.08.2026.
USB,USB-A connector,"female right-angle, socket for a USB stick (J4)",1,THT,TME (USB-A-S-RA),unchanged
USB,TS3USB221DRCR,USB 2.0 analogue mux (U9),1,VSON-10,LCSC (C324071),unchanged
USB,SY6280AAC,current-limited 5 V switch (U10),1,SOT-23-5,LCSC (C55136),unchanged
Other,Pin header 1x40,"male, cut down for J6 (1x3)",1,"THT, 2,54 mm",TME (ZL201-40G),unchanged
Other,Female socket strip 1x40,"cut down for J5 (1x8), the LCD module",1,"THT, 2,54 mm",TME (ZL262-40SG),unchanged
NEW THT,Resistor 10 kΩ,"pull-ups R9-R14, pull-down R15, VBUS sense R22, SW6 ladder R28/R29",10,"metal film 0,6 W 1 %, axial, 10,16 mm pitch",Chipoteka,"series ""R 0,6 W 1%"", package 0207 (6,3 x 2,5 mm)"
NEW THT,"Resistor 6,8 kΩ","SY6280 ISET (R19), pull-ups for the SW6 axes (R26, R27)",3,"metal film 0,6 W 1 %, axial, 10,16 mm pitch",Chipoteka,"series ""R 0,6 W 1%"""
NEW THT,Resistor 51 kΩ,"upper members of the feedback dividers (R16, R24)",2,"metal film 0,6 W 1 %, axial, 10,16 mm pitch",Chipoteka,"series ""R 0,6 W 1%"""
NEW THT,Resistor 24 kΩ,"CH224K CFG1, selects the 12 V PD profile (R23)",1,"metal film 0,6 W 1 %, axial, 10,16 mm pitch",Chipoteka,"series ""R 0,6 W 1%"""
NEW THT,Resistor 1 kΩ,series VBUS -> VDD of the CH224K controller (R21),1,"metal film 0,6 W 1 %, axial, 10,16 mm pitch",Chipoteka,"series ""R 0,6 W 1%"""
NEW THT,Resistor 120 Ω,CAN termination at the connector (R7),1,"metal film 0,6 W 1 %, axial, 10,16 mm pitch",Chipoteka,"series ""R 0,6 W 1%"""
NEW THT,Resistor 33 Ω,series on the display BL input (R8),1,"metal film 0,6 W 1 %, axial, 10,16 mm pitch",Chipoteka,"series ""R 0,6 W 1%"""
NEW THT,Resistor 15 kΩ,"lower member of the 3,3 V divider, upper half (R17A)",1,"metal film 0,6 W 1 %, axial, 10,16 mm pitch",Chipoteka,"IN SERIES with R17B: 15k + 470R = 15,47 kΩ, output 3,300 V. Substitute for the unobtainable 15,4 kΩ (06.08.2026.). 15 kΩ ALONE is not enough, it gives 3,38 V"
NEW THT,Resistor 470 Ω,"lower member of the 3,3 V divider, lower half (R17B)",1,"metal film 0,6 W 1 %, axial, 10,16 mm pitch",Chipoteka,"IN SERIES with R17A: 15k + 470R = 15,47 kΩ, output 3,300 V. An alternative 390 Ω gives 3,313 V and passes equally. The 1 % tolerance is mandatory because it sets the output voltage"
NEW THT,"Resistor 9,31 kΩ",lower member of the 5 V divider (R25),1,"metal film 0,6 W 1 %, axial, 10,16 mm pitch",Chipoteka,"E96 value. If unavailable, 9,1 kΩ gives 5,07 V instead of 4,98 V, which is acceptable"
NEW THT,Capacitor 100 nF,"decoupling and bootstrap (C10-C16, C20, C21, C23, C24, C29)",12,"ceramic disc, RM 5 mm, >= 50 V",Chipoteka,Chipoteka stocks ceramics on a 5 mm pitch and the footprint is matched to that
NEW THT,Capacitor 22 pF,"crystal load (C6, C7)",2,"ceramic disc NP0, RM 5 mm",Chipoteka,same 5 mm pitch
NEW THT,Capacitor 1 µF,"VDD of the CH224K controller (C22), RC on the module EN pin (C26)",2,"ceramic / multilayer, RM 5 mm",Chipoteka,same 5 mm pitch
NEW THT,Capacitor 10 µF,"bulk per section (C5, C18, C19, C25) and at the input of switch U10 (C37)",5,"radial electrolytic, >= 25 V, D5 mm, 2 mm pitch",Chipoteka,"polarised, anode to the supply. C37 sits on the 5 V rail so >= 10 V is enough for it, but the same 25 V part passes. C37 added 09.08.2026.: the input of switch U10 had only 100 nF and the nearest electrolytic was 73 mm away"
NEW THT,Capacitor 22 µF low ESR,"input and output of both converters (C3, C4, C27, C28)",4,"radial, up to Ø6,3 mm, the footprint is 2,5 mm pitch but also takes 2,0 mm",Chipoteka,"THE CRITERION IS IMPEDANCE, NOT CHEMISTRY (10.08.2026.): ESR at 100 kHz <= 0,15 Ω and rated ripple current >= 0,35 A rms. They carry 0,88 A pp on 3,3 V and 1,07 A pp on 5 V, so 0,15 Ω keeps the ripple at 132 and 161 mV. A polymer part meets it (20 to 50 mΩ), as does an electrolytic marked low ESR or low impedance, but NOT a plain electrolytic (about 1 Ω gives 878 mV and pushes the ESP32-S3 and the flash out of specification). If the ESR is worse, add a ceramic 4,7 to 10 µF across the same pads. The low ESR electrolytics already bought, Ø5 mm / 2,0 mm pitch, are used with their leads eased out to 2,5 mm"
NEW THT,Capacitor 100 µF,input bulk on VBUS (C1),1,"radial electrolytic, 25 V, D6,3 mm, 2,5 mm pitch",Chipoteka,polarised
NEW THT,"Inductor 4,7 µH","buck converters (L2, L3)",2,"radial, 5,00 mm pitch, body up to Ø8,5 mm, up to 12 mm tall",Conrad,"CHANGED from 10 µH 09.08.2026. Table 7-2 of the TPS562201 datasheet gives 4,7 µH as the maximum for both 3,3 V and 5 V, and 10 µH was more than double that. With low ESR output capacitors the ripple current at 4,7 µH is 0,25 to 0,31 A rms, which such a part handles easily. Ask for Isat >= 1,5 A and DCR up to 0,1 Ω. On 10.08.2026. the footprint was changed to a radial one (L_Radial_D8.7mm_P5.00mm_Fastron_07HCP), because the part bought is radial too: 4,3 A, 30 mΩ, body Ø8,5 x 11 mm, 5,0 mm lead pitch. An axial footprint draws the body over one hole, while a radial part sits centred between two. Before that the footprint had been enlarged from Ø5,0 to Ø7,5 mm, because it drew a smaller body than the BOM asks for"
Power,SMAJ16A-13-F,TVS on the 12 V rail towards pin 16 (D2) and the blocking diode on the same rail (D3),2,SMA (DO-214AC),"TME, LCSC","back to SMD 05.08.2026.; cathode (pad 1) to OBD_12V, polarity corrected. QUANTITY BACK TO 2 (10.08.2026.): D3 is an SMAJ16A again, the request for a Schottky SS34 was withdrawn. Both pieces sit in the same orientation so they cannot be swapped by mistake"
Power,1206L050YR,"PTC fuse 0,5 A on the 12 V rail (F1)",1,1206,"TME, LCSC",back to SMD 05.08.2026.
Mechanics,PCB fabrication,"2 layers, 130 x 115 mm, FR4 1,6 mm, min. 5 pieces (v0.7)",1,-,"JLCPCB, PCBWay, Aisler",size raised from 115 x 100 because of 17 new footprints and the tighter grouping around the ICs
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
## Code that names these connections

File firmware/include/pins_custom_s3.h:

// pins_custom_s3.h
// GPIO assignment for the ESP32-S3-WROOM-1 module: the single hardware-first target,
// used on the breadboard adapter during development and on the dedicated PCB.
// This is the authoritative map:
// analog inputs on ADC1 (GPIO1-10), strapping pins (3, 45, 46) and the
// flash/octal-PSRAM range (GPIO26-37) avoided. GPIO0 keeps its standard
// strapping role only: the BOOT button (SW4), never a firmware signal.
#pragma once

// Shared SPI bus (FSPI)
constexpr int PIN_SPI_SCK  = 12;
constexpr int PIN_SPI_MISO = 13;
constexpr int PIN_SPI_MOSI = 11;

// CAN controller (MCP2515)
constexpr int PIN_CS_CAN   = 10;
constexpr int PIN_INT_CAN  = 9;

// Display (ILI9341) - also configured for TFT_eSPI via build flags
constexpr int PIN_CS_TFT   = 14;
constexpr int PIN_DC_TFT   = 21;
constexpr int PIN_RST_TFT  = 47;

// Memory
constexpr int PIN_CS_FLASH = 15;  // W25Q128 (primary storage, FAT filesystem)

// USB (v0.5): one OTG controller on fixed pins, switched between the USB-C
// connector (MSC device, PC link) and the USB-A receptacle (stick host) by
// the TS3USB221 analog mux, and stick VBUS goes through the SY6280 load switch.
// A hardware-first pull-down (R15) holds the mux select LOW while no firmware
// drives it, so at reset the OTG pins face USB-C and the ROM bootloader's
// USB-Serial-JTAG is reachable for flashing (see "Programming" below).
constexpr int PIN_USB_DN      = 19;  // fixed OTG D- (informational)
constexpr int PIN_USB_DP      = 20;  // fixed OTG D+ (informational)
// Mux select: LOW = USB-C, HIGH = USB-A. The firmware KEEPS IT LOW in normal
// operation and raises it only for the duration of a stick session, so the
// ROM's USB-Serial-JTAG stays reachable from a PC and uploads need no button
// presses (see pins_init_normal_mode in src/storage/usb_msc_device.cpp).
constexpr int PIN_USB_SEL     = 16;
// 5 V load-switch enable for USB-A, active high, with a 10 k pull-down (R37)
// so the stick supply stays off until the firmware asks for it.
constexpr int PIN_USB_HOST_EN = 17;

// Programming (informational - none of these are driven by the firmware).
// Upload runs over USB-C via the ROM USB-Serial-JTAG on the fixed OTG pins:
// `pio run -e custom-board -t upload`, with no button presses. The running
// application never calls USB.begin(), so the USB PHY stays routed to the
// USB-Serial-JTAG controller instead of the OTG one, and the mux stays on
// the USB-C side, so esptool sees a port and resets the chip itself.
//
// The manual path - hold BOOT (SW4, GPIO0 low), tap RESET (SW5, EN), release
// BOOT, then upload - is needed only when that port is genuinely gone: in the
// MSC device role (USB.begin() has taken the OTG controller) or when the
// firmware hangs before pins_init_normal_mode() runs.
//
// The serial monitor stays on UART0 (ARDUINO_USB_CDC_ON_BOOT=0) and is
// exposed on header J6 for an external USB-UART adapter. That header carries
// only TX, RX and GND, so the UART path always needs the two buttons.
constexpr int PIN_BOOT_BTN    = 0;   // SW4 to GND, 10 k pull-up (R14)
constexpr int PIN_UART0_TX    = 43;  // J6 pin 1, 115200 baud monitor
constexpr int PIN_UART0_RX    = 44;  // J6 pin 2

// User interface (EN11 incremental encoder, SKRHABE010 5-way switch, three buttons).
// v0.7: the analog stick and its J3 header were replaced by the on-board
// Alps SKRHABE010. JOY_X/JOY_Y stay on the same ADC pins but now carry a
// three-level resistor ladder (idle ~3,3 V / 10 k ladder ~1,96 V / 0 V),
// decoded in ui/input.cpp.
// ENC1 = BI Technologies EN11-HSB1AQ20, incremental, 20 detents/turn, with
// push switch (board v0.8). It replaced the RK12L12 potentiometer: A took
// over the old POT net on GPIO1, B and the switch use two module pins that
// were previously unconnected. GPIO1 is still an ADC pin but is now used
// digitally.
//
// Board v0.9/v0.9b fit an external filter on all three contacts, so the
// internal pull-ups are no longer the only thing holding the lines: 100 R in
// series at the contact (R38-R40), then a 10 k pull-up and 47 nF to ground
// (R32-R34, C31-C33), and 1 nF at the module pin (C34-C36). The rise time is
// therefore ~650 us to the input threshold, which is well inside the ~5 ms
// edge spacing of the fastest realistic turn - the ISR decoding below does not
// need to change. (This comment used to say "no external parts are fitted",
// which stopped being true with board v0.9.)
constexpr int PIN_ENC_A       = 1;   // quadrature channel A (was PIN_POT)
constexpr int PIN_ENC_B       = 38;  // quadrature channel B
constexpr int PIN_ENC_SW      = 39;  // encoder push switch, active low
constexpr int PIN_JOY_X       = 2;   // ADC1_CH1, SW6 A (direct) / B (ladder)
constexpr int PIN_JOY_Y       = 4;   // ADC1_CH3, SW6 C (direct) / D (ladder)
// SW6 centre push, active low, R9 pull-up - ON PAPER. On the assembled v0.7
// board this pin is really the switch's COMMON terminal, because the footprint's
// pin numbering does not match the part (found by measurement 21.08.2026.).
// The firmware holds it LOW so the four directions work at all, and releases it
// for a few hundred microseconds to read the centre. NEVER drive it HIGH: with
// the centre pressed that is a short to ground. Full account in
// ui/input.cpp and hardware/kicad/PROVJERITI-PRIJE-IZRADE.md.
constexpr int PIN_JOY_SW      = 5;
constexpr int PIN_BTN_CONFIRM = 6;   // active low, external pull-up
constexpr int PIN_BTN_CLEAR   = 7;   // active low, external pull-up
constexpr int PIN_BTN_RETURN  = 8;   // active low, external pull-up

// S3 pins are all full I/O, so internal pull-ups exist as a fallback.
constexpr bool PIN_BTN_NEEDS_EXTERNAL_PULLUP = false;

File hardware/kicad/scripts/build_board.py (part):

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    # the J1962F connector, so the diagnostic tool is powered as it is in a car.
    "PD_VDD", "PD_SENSE", "PD_CFG1",
    "CANH", "CANL", "CAN_TX", "CAN_RX", "XTAL1", "XTAL2",
    # SCK_MCU / MOSI_MCU: the stub between the microcontroller pin and the series
    # resistor (R30, R31). Past the resistor lies the SCK / MOSI bus carrying
    # U4, U7 and J5. The split was introduced because the bus is about 100 mm
    # long with three loads and had no termination at all.
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    # (idle 3,3 V / ladder ~1,96 V / direct 0 V) on JOY_X and JOY_Y.
    # ENC_A/ENC_B: the quadrature outputs of the incremental encoder ENC1,
    # ENC_SW is its built-in push-button. They replaced the POT net of the
    # former potentiometer RV1, and ENC_A took over GPIO1, that is the existing
    # potentiometer trace.
    "ENC_A", "ENC_B", "ENC_SW",
    # ENC_*_RAW: the stub from the encoder contact itself to the series resistor
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    ("C6", "Capacitor_THT", C_TINY[1], 24, 53, 0, "22pF", {"1": "XTAL1", "2": G}),
    ("C7", "Capacitor_THT", C_TINY[1], 24, 47, 0, "22pF", {"1": "XTAL2", "2": G}),
    # SN65HVD230DR replaced the obsolete MCP2551-I/SN (18.07.2026.): same
    # SOIC-8 pinout (TXD/GND/VCC/RXD/Vref/CANL/CANH/RS), RS to GND is
    # high-speed mode on both, and the HVD230 is a native 3,3 V part - the
    # MCP2551 wanted 4,5-5,5 V and was being run out of spec on this rail.
    ("U5", "Package_SO", "SOIC-8_3.9x4.9mm_P1.27mm", 13, 33, 90, "SN65HVD230DR", {
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    # edge and the signals leaving U6 had no escape eastward (JOY_SW and
    # CS_FLASH failed to route in every attempt).
    # The anchor is pin 1 and the pins run downward on a 2,54 mm pitch. At
    # y = 44,2, pin 5 (CS_TFT) lands on y = 34,0, exactly level with pin U6.22
    # where that signal starts, so the trace runs due east. At y = 34 the signal
    # had to cut diagonally through the congested band and did not get through.
    ("J5", "Connector_PinHeader_2.54mm", "PinHeader_1x08_P2.54mm_Vertical", 56, 44.2, 0, "LCD 18366", {
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    ("C36", "Capacitor_THT", C_TINY[1], 60, 26, 0, "1nF", {"1": "ENC_SW", "2": G}),
    #
    # 3) Blocking diode in the 12 V branch. The path used to be
    #    VBUS -> F1 -> OBD_12V -> pin 16, and F1 is a PTC that conducts in both
    #    directions, so external 12 V from a vehicle or from a tool that powers
    #    pin 16 itself would flow back into VBUS, into both converter inputs and
    #    onto the USB-C connector. The diode passes only the intended direction:
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    }),
    #
    # 7) Pull-ups on the chip-select lines. Until the firmware claims the pin,
    #    CS_CAN (GPIO10) and CS_FLASH (GPIO15) float, so the MCP2515 and the
    #    flash can see a spurious selection. 10 k to 3,3 V holds them inactive.
    ("R35", "Resistor_THT", R_THT[1], 22, 38, 0, "10k", {"1": V3, "2": "CS_CAN"}),
    ("R36", "Resistor_THT", R_THT[1], 68, 44, 0, "10k", {"1": V3, "2": "CS_FLASH"}),
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    "C12": ("U5", "3"),  "C5":  ("U5", "3"),     # CAN transceiver VDD
    # Termination and ESD right at the OBD connector.
    #
    # The anchor is pin 14 (CANL), not pin 6 (CANH). The reason is connector
    # geometry, not electronics. The J1962F body is 43,3 x 20,7 mm and its
    # contacts lie INSIDE that body: pin 14 is 6,3 mm from the lower edge of the
    # housing, pin 6 as much as 14,9 mm. Nothing can be placed inside the body,
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    "R33": ("R39", "2"),   "C32": ("R39", "2"),
    "R34": ("R40", "2"),   "C33": ("R40", "2"),
    # The other end of the same line: a capacitor right at the module input pin.
    # U6 pin 39 = GPIO1 (ENC_A), 31 = GPIO38 (ENC_B), 32 = GPIO39 (push-button).
    "C34": ("U6", "39"), "C35": ("U6", "31"), "C36": ("U6", "32"),
    # Blocking diode next to the fuse, so the 12 V branch stays one short line
    # VBUS -> F1 -> D3 -> pin 16.
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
